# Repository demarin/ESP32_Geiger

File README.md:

# ESP32_Geiger

Практическая работа “Счетчик Гейгера”

Все, наверное, знают, что такое счетчик Гейгера, и у некоторых он даже есть дома. 

С этими счетчиками есть две небольшие проблемы. Во-первых, они достаточно дорогие, и цены на них в последнее время резко пошли вверх. Во-вторых, большинство таких счетчиков не имеют возможности вести измерения в автоматическом режиме и передавать данные на компьютер.

Цель проекта – разработать счетчик Гейгера, который мог бы собрать любой желающий с минимальными умениями в области электроники. 

Во время летней школы в 2022 году был собран прототип устройства.

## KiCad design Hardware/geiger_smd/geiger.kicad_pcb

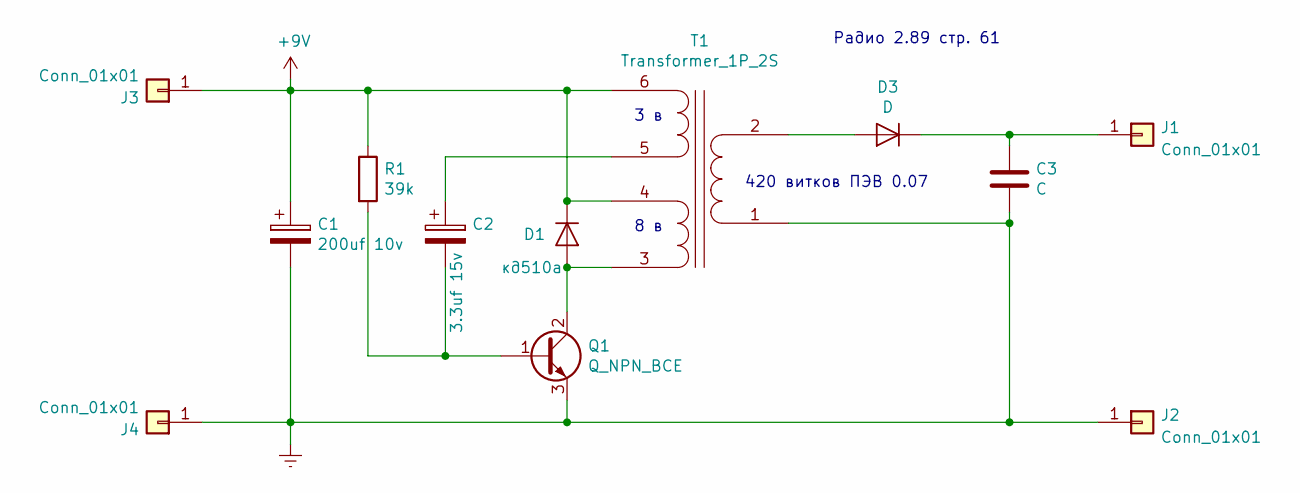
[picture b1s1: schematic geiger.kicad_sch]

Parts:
C1: 200uf 10v; CP_Radial_D10.0mm_P2.50mm_P5.00mm
C2: 3.3uf 15v; CP_Radial_D6.3mm_P2.50mm
C3: C; C_Rect_L28.0mm_W8.0mm_P22.50mm_MKS4
D1: кд510а; D_DO-41_SOD81_P5.08mm_Vertical_AnodeUp
D3: D; D_DO-35_SOD27_P12.70mm_Horizontal
J1, J2, J3, J4: Conn_01x01; Pin_Header_Straight_1x01_Pitch2.54mm
Q1: Q_NPN_BCE; SOT-223-3_TabPin2
R1: 39k; R_Axial_DIN0207_L6.3mm_D2.5mm_P10.16mm_Horizontal
T1: Transformer_1P_2S; Pin_Header_Straight_1x06_Pitch2.54mm

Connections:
+9V: C1.1, D1.1 (K), J3.1, R1.1, T1.4 (SB), T1.6 (SD)
Earth: C1.2, C3.1, J2.1, J4.1, Q1.3 (E), T1.1 (AA)
unnamed: C2.1, T1.5 (SC)
unnamed: C2.2, Q1.1 (B), R1.2
unnamed: C3.2, D3.1 (K), J1.1
unnamed: D1.2 (A), Q1.2 (C), T1.3 (SA)
unnamed: D3.2 (A), T1.2 (AB)

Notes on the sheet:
420 витков ПЭВ 0.07
Радио 2.89 стр. 61
3 в
8 в

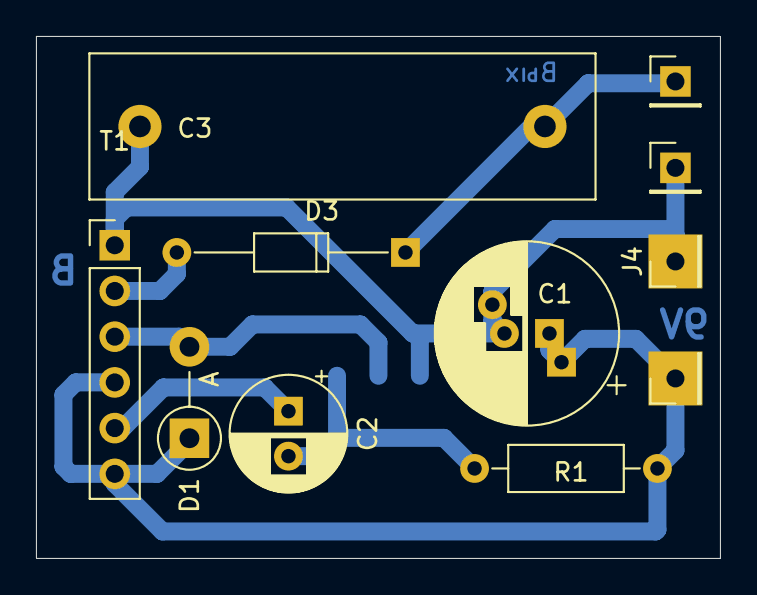
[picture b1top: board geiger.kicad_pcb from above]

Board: 2 copper layers, 38.0 x 29.0 mm, 12 parts (1 on the bottom side), 7 nets.

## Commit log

2022-08-05 ADc and PWM
2022-08-07 Add files via upload
    write to file without deleting previous values
